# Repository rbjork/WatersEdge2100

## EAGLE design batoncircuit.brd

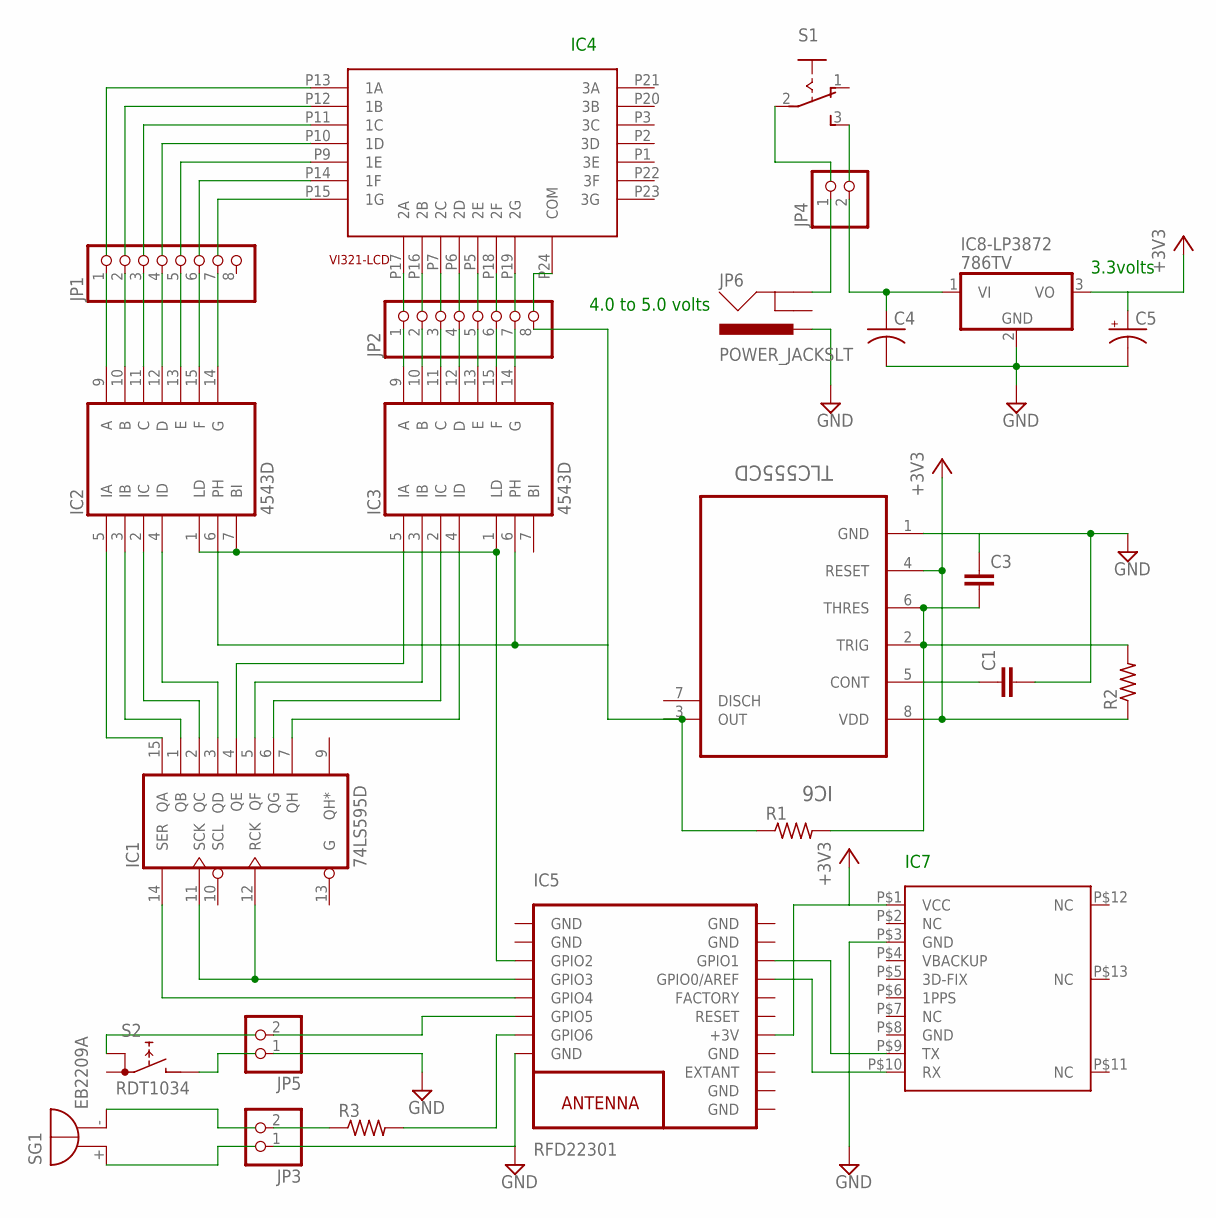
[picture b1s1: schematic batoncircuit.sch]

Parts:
C1: C-EU075-063X106; C075-063X106
C3: C-EUC1812; C1812
C4: C-US050-045X075; C050-045X075
C5: CPOL-USE5-10.5; E5-10,5
IC1: 74LS595D; SO16
IC2, IC3: 4543D; SO16
IC5: RFD22301
IC6: TLC555CD; SOIC127P600X175-8N
IC7: GPS_FGPMMOPA6C; FGPMMOPA6C
IC8-LP3872: 786TV; TO220V
JP1, JP2: PINHD-1X8; 1X08
JP3, JP4, JP5: PINHD-1X2; 1X02
JP6: POWER_JACKSLT; POWER_JACK_SLOT
R1, R2: R-US_0207/10; 0207/10
R3: R-US_0207/12; 0207/12
S1: 255SB
S2: RDT1034
SG1: EB2209A
U8: V321-3DIGIT-LCD; VI321-3DIGIT-LCD

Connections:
+3V3: IC5.13 (+3V), IC6.4 (RESET), IC6.8 (VDD), IC7.P$1 (VCC), R2.1
GND: C1.2, C3.1, C4.2, C5.-, IC1.8 (GND), IC5.1 (GND), IC5.2 (GND), IC5.8 (GND), IC5.9 (GND), IC5.10 (GND), IC5.12 (GND), IC5.18 (GND), IC5.19 (GND), IC6.1 (GND), IC7.P$3 (GND), IC8-LP3872.2 (GND), JP3.1, JP5.1, JP6.PWR
unnamed: IC2.9 (A), JP1.1
unnamed: IC2.10 (B), JP1.2
unnamed: IC2.11 (C), JP1.3
unnamed: IC2.12 (D), JP1.4
unnamed: IC2.13 (E), JP1.5
unnamed: IC2.15 (F), JP1.6
unnamed: IC2.14 (G), JP1.7
unnamed: IC1.15 (QA), IC2.5 (IA)
unnamed: IC1.1 (QB), IC2.3 (IB)
unnamed: IC1.2 (QC), IC2.2 (IC)
unnamed: IC1.3 (QD), IC2.4 (ID)
unnamed: IC1.7 (QH), IC3.4 (ID)
unnamed: IC1.6 (QG), IC3.2 (IC)
unnamed: IC1.5 (QF), IC3.3 (IB)
unnamed: IC1.4 (QE), IC3.5 (IA)
unnamed: IC2.6 (PH), IC3.6 (PH), IC6.3 (OUT), JP2.8, R1.1
unnamed: IC1.14 (SER), IC5.5 (GPIO4)
unnamed: C1.1, IC6.5 (CONT)
unnamed: IC5.16 (GPIO0/AREF), IC7.P$10 (RX)
unnamed: C3.2, IC6.2 (TRIG), IC6.6 (THRES), R1.2, R2.2
unnamed: IC5.17 (GPIO1), IC7.P$9 (TX)
unnamed: IC2.1 (LD), IC2.7 (BI), IC3.1 (LD), IC5.3 (GPIO2)
unnamed: JP3.2, R3.1
unnamed: C4.1, IC8-LP3872.1 (VI), JP4.2
unnamed: IC5.7 (GPIO6), R3.2
unnamed: IC1.11 (SCK), IC1.12 (RCK), IC5.4 (GPIO3)
unnamed: IC3.14 (G), JP2.7
unnamed: IC3.15 (F), JP2.6
unnamed: IC3.13 (E), JP2.5
unnamed: IC3.12 (D), JP2.4
unnamed: IC3.11 (C), JP2.3
unnamed: IC3.10 (B), JP2.2
unnamed: IC3.9 (A), JP2.1
unnamed: C5.+, IC8-LP3872.3 (VO)
unnamed: JP4.1, JP6.GND@2 (GND)
unnamed: IC5.6 (GPIO5), JP5.2
VCC: IC1.16 (VCC)
VDD: IC2.16 (VDD), IC3.16 (VDD)
VSS: IC2.8 (VSS), IC3.8 (VSS)

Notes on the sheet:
4.0 to 5.0 volts
3.3volts
IC7
IC4

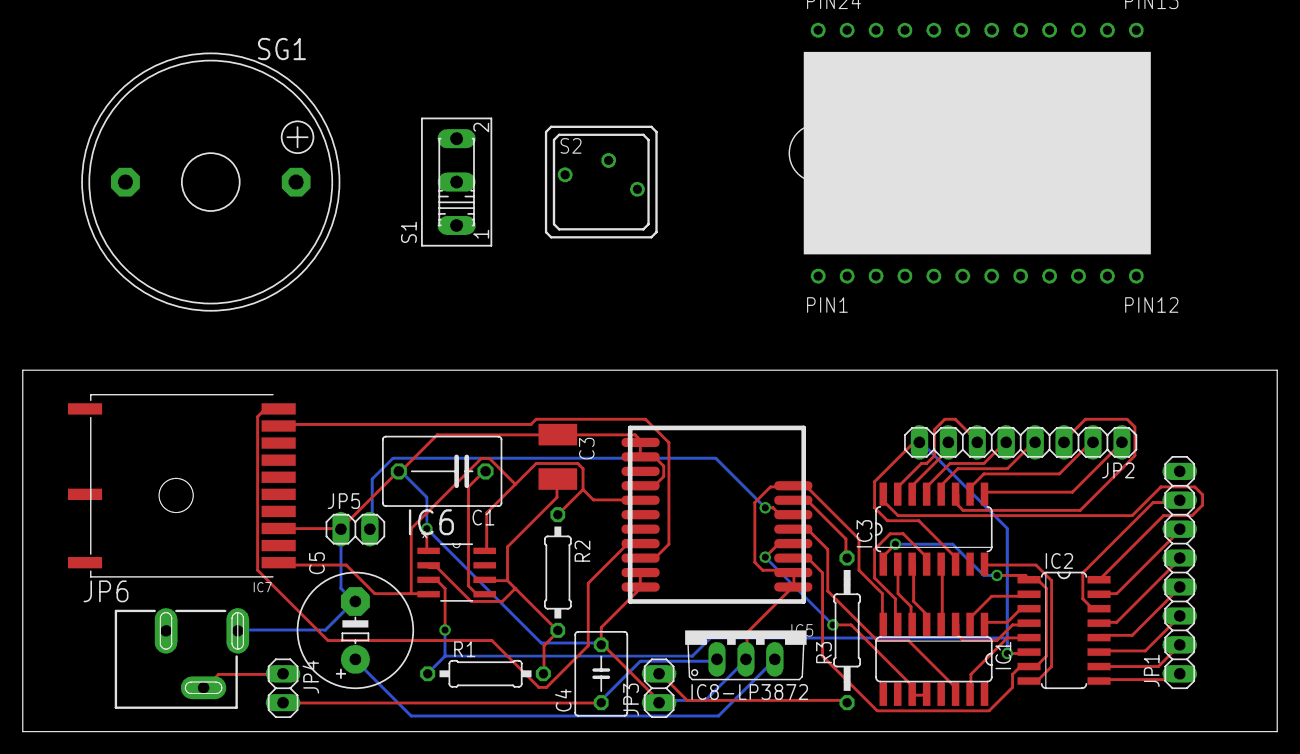
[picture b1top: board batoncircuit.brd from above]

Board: 2 copper layers, 110.2 x 31.7 mm, 24 parts (0 on the bottom side), 40 nets.

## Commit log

2015-06-02 Files for creating baton electronics
    Contains Eagle files for schematic and PCB board. May need addition of
    Texas Instructions lbr
2015-06-03 Adafruit GPS SDK
    This folder contains the software libraries needed by the Arduno MCU to
    communicate with the GPS chip.
2015-06-04 Added statement on completeness of baton code
2015-06-08 Switches and jack addition
    Added power jack, marker switch and power switch along with connecting
    pins on board.
2015-06-09 Unload of Relay Event Server
    Contains all basic queries but needs admin pages and geo data
    implementation
2015-06-12 Addition of Rest calls for markers
    Same
2015-06-16 Addition of compaass utiliazation in RelayRunServer
    Added methods to SLR controller

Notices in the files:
parts and their libraries:
SparkFun-Connectors: Licensing: Creative Commons ShareAlike 4.0 International - https://creativecommons.org/licenses/by-sa/4.0
